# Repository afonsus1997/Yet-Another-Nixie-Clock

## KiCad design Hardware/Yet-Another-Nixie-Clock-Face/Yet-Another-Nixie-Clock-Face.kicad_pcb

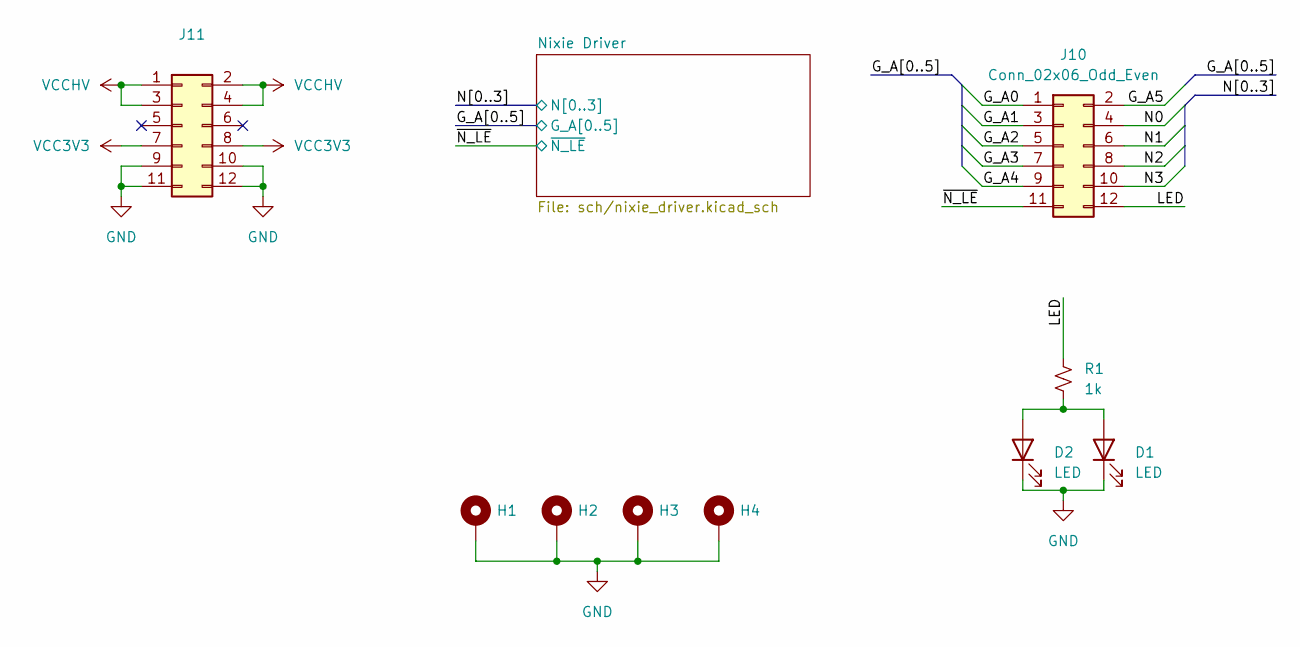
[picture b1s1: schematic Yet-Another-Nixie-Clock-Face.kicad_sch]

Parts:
D1, D2: LED; LED_0603_1608Metric
H1, H2, H3, H4: MountingHole_Pad; MountingHole_3.2mm_M3_Pad
J10, J11: Conn_02x06_Odd_Even; PinHeader_2x06_P2.54mm_Vertical_SMD; LCSC C3294464
R1: 1k; R_0603_1608Metric; LCSC C22548

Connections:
/G_A0: J10.1; also elsewhere on the board
/G_A1: J10.3; also elsewhere on the board
/G_A2: J10.5; also elsewhere on the board
/G_A3: J10.7; also elsewhere on the board
/G_A4: J10.9; also elsewhere on the board
/G_A5: J10.2; also elsewhere on the board
/LED: J10.12, R1.2
/N0: J10.4; also elsewhere on the board
/N1: J10.6; also elsewhere on the board
/N2: J10.8; also elsewhere on the board
/N3: J10.10; also elsewhere on the board
/~N_LE: J10.11; also elsewhere on the board
GND: D1.1 (K), D2.1 (K), H1.1, H2.1, H3.1, H4.1, J11.9, J11.10, J11.11, J11.12; also elsewhere on the board
unnamed: D1.2 (A), D2.2 (A), R1.1
VCC3V3: J11.7, J11.8; also elsewhere on the board
VCCHV: J11.1, J11.2, J11.3, J11.4; also elsewhere on the board

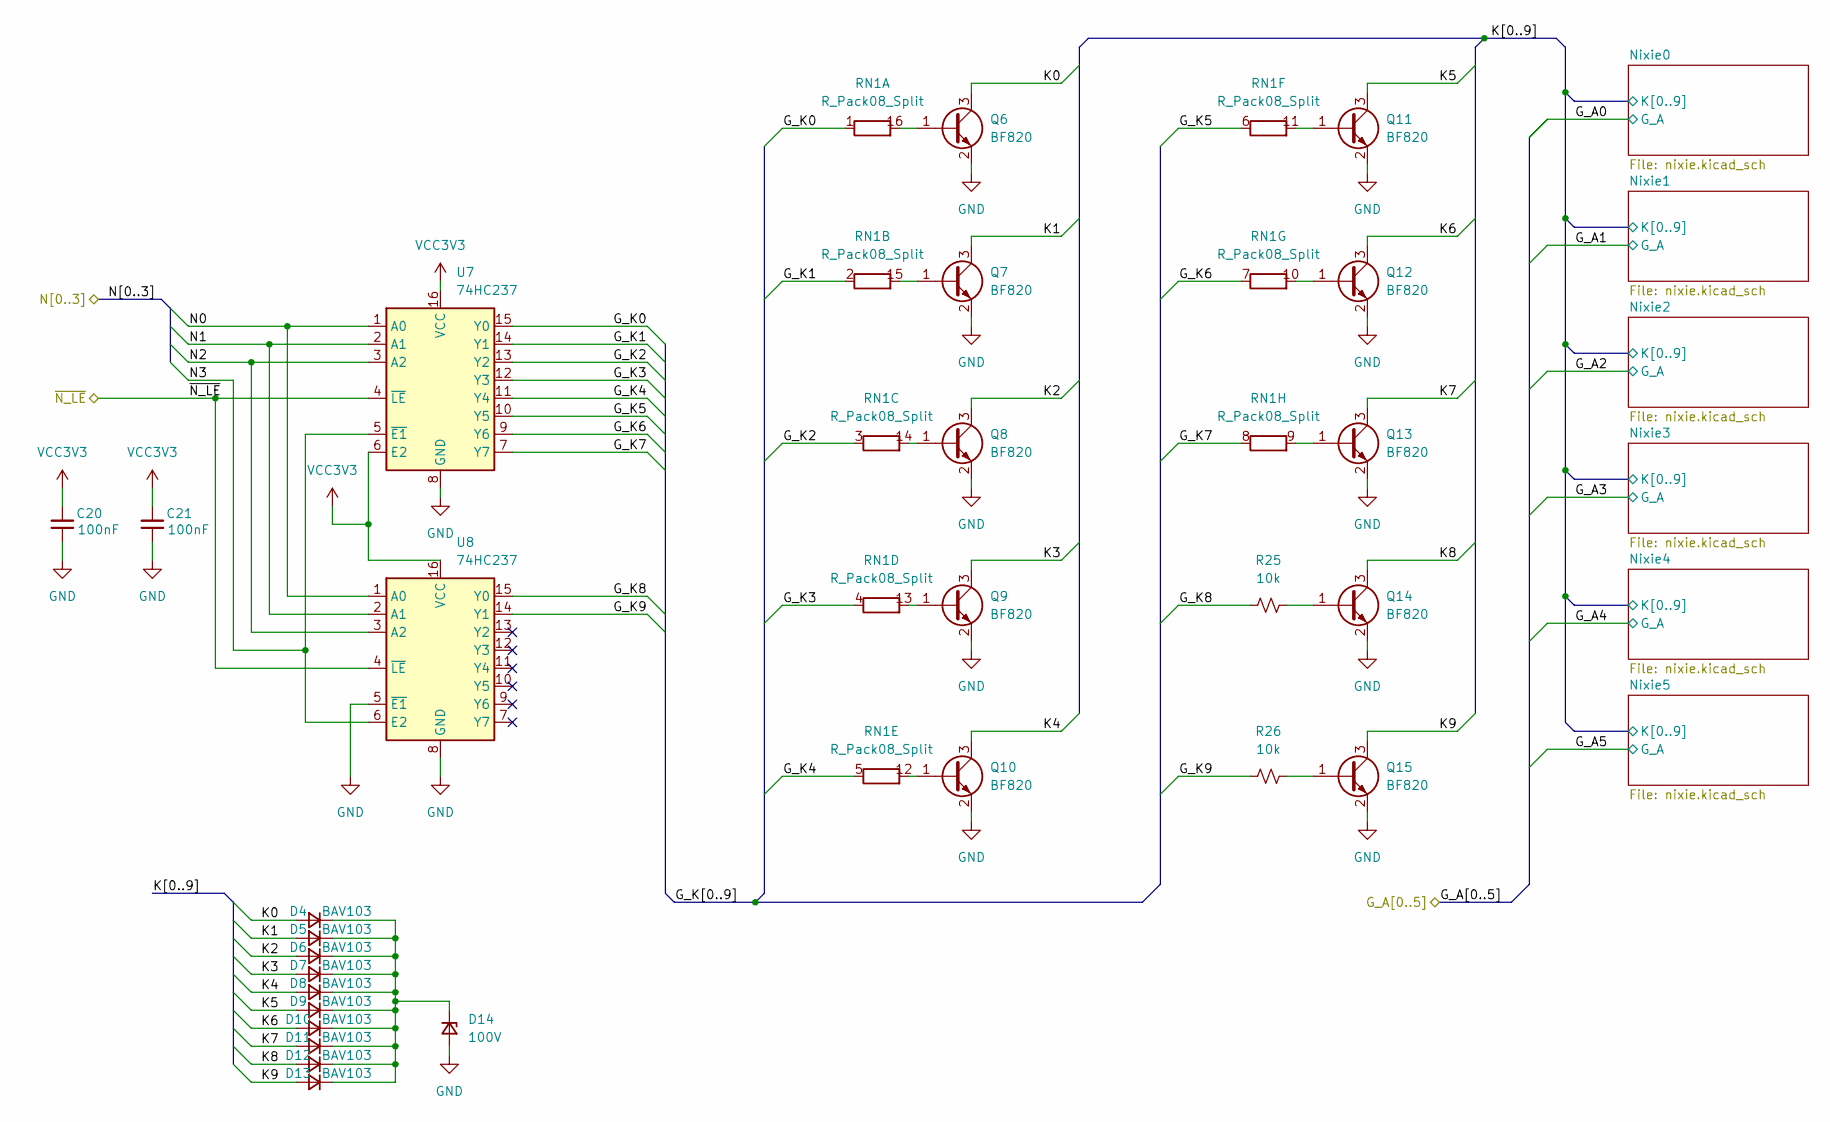
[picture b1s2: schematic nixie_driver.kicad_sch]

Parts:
C20, C21: 100nF; C_0603_1608Metric; LCSC C92490
D4, D5, D6, D7, D8, D9, D10, D11, D12, D13: BAV103; D_MiniMELF; LCSC C3313132
D14: 100V; D_SMA; LCSC C3014322
Q6, Q7, Q8, Q9, Q10, Q11, Q12, Q13, Q14, Q15: BF820; TSOT-23; LCSC C426796
R25, R26: 10k; R_0603_1608Metric; LCSC C98220
RN1: R_Pack08_Split; RES-ARRAY-SMD_0402-16P-L4.0-W1.6-BL-2; LCSC C326649
U7, U8: 74HC237; TSSOP-16_4.4x5mm_P0.65mm; LCSC C2674656

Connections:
/N0: U7.1 (A0), U8.1 (A0); also elsewhere on the board
/N1: U7.2 (A1), U8.2 (A1); also elsewhere on the board
/N2: U7.3 (A2), U8.3 (A2); also elsewhere on the board
/N3: U7.5 (~E1), U8.6 (E2); also elsewhere on the board
/Nixie Driver/G_K0: RN1.1 (R1.1), U7.15 (Y0)
/Nixie Driver/G_K1: RN1.2 (R2.1), U7.14 (Y1)
/Nixie Driver/G_K2: RN1.3 (R3.1), U7.13 (Y2)
/Nixie Driver/G_K3: RN1.4 (R4.1), U7.12 (Y3)
/Nixie Driver/G_K4: RN1.5 (R5.1), U7.11 (Y4)
/Nixie Driver/G_K5: RN1.6 (R6.1), U7.10 (Y5)
/Nixie Driver/G_K6: RN1.7 (R7.1), U7.9 (Y6)
/Nixie Driver/G_K7: RN1.8 (R8.1), U7.7 (Y7)
/Nixie Driver/G_K8: R25.1, U8.15 (Y0)
/Nixie Driver/G_K9: R26.1, U8.14 (Y1)
/Nixie Driver/K0: D4.2 (A), Q6.3 (C); also elsewhere on the board
/Nixie Driver/K1: D5.2 (A), Q7.3 (C); also elsewhere on the board
/Nixie Driver/K2: D6.2 (A), Q8.3 (C); also elsewhere on the board
/Nixie Driver/K3: D7.2 (A), Q9.3 (C); also elsewhere on the board
/Nixie Driver/K4: D8.2 (A), Q10.3 (C); also elsewhere on the board
/Nixie Driver/K5: D9.2 (A), Q11.3 (C); also elsewhere on the board
/Nixie Driver/K6: D10.2 (A), Q12.3 (C); also elsewhere on the board
/Nixie Driver/K7: D11.2 (A), Q13.3 (C); also elsewhere on the board
/Nixie Driver/K8: D12.2 (A), Q14.3 (C); also elsewhere on the board
/Nixie Driver/K9: D13.2 (A), Q15.3 (C); also elsewhere on the board
/~N_LE: U7.4 (~LE), U8.4 (~LE); also elsewhere on the board
GND: C20.1, C21.1, D14.2 (A), Q6.2 (E), Q7.2 (E), Q8.2 (E), Q9.2 (E), Q10.2 (E), Q11.2 (E), Q12.2 (E), Q13.2 (E), Q14.2 (E), Q15.2 (E), U7.8 (GND), U8.5 (~E1), U8.8 (GND); also elsewhere on the board
unnamed: D4.1 (K), D5.1 (K), D6.1 (K), D7.1 (K), D8.1 (K), D9.1 (K), D10.1 (K), D11.1 (K), D12.1 (K), D13.1 (K), D14.1 (K)
unnamed: Q6.1 (B), RN1.16 (R1.2)
unnamed: Q7.1 (B), RN1.15 (R2.2)
unnamed: Q8.1 (B), RN1.14 (R3.2)
unnamed: Q9.1 (B), RN1.13 (R4.2)
unnamed: Q10.1 (B), RN1.12 (R5.2)
unnamed: Q11.1 (B), RN1.11 (R6.2)
unnamed: Q12.1 (B), RN1.10 (R7.2)
unnamed: Q13.1 (B), RN1.9 (R8.2)
unnamed: Q14.1 (B), R25.2
unnamed: Q15.1 (B), R26.2
VCC3V3: C20.2, C21.2, U7.6 (E2), U7.16 (VCC), U8.16 (VCC); also elsewhere on the board

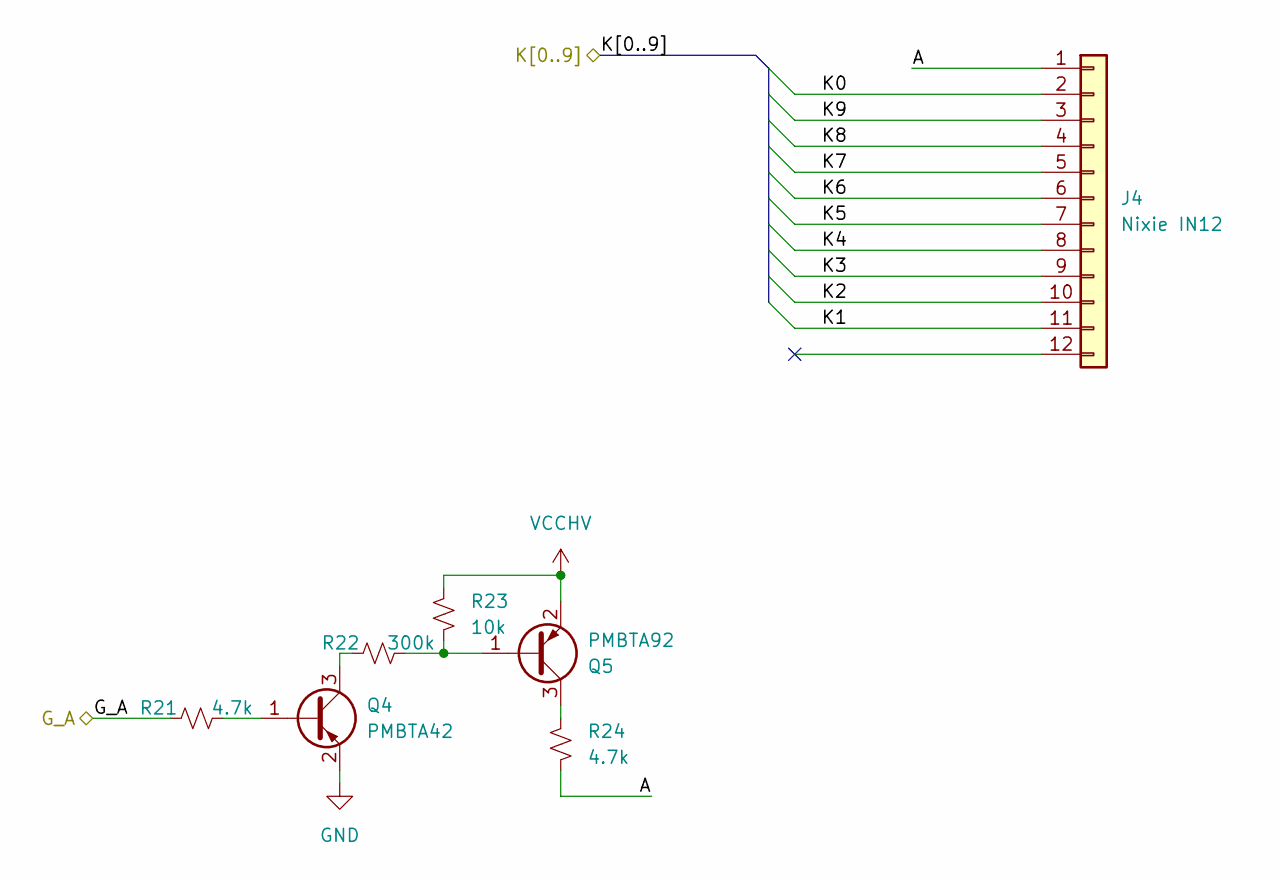
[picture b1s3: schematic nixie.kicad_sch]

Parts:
J4: Nixie IN12; IN_12B_Socket
Q4: PMBTA42; SOT-23; LCSC C417384
Q5: PMBTA92; SOT-23; LCSC C282560
R21, R24: 4.7k; R_0603_1608Metric; LCSC C99782
R22: 300k; R_0603_1608Metric; LCSC C114667
R23: 10k; R_0603_1608Metric; LCSC C98220

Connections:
/G_A0: R21.2; also elsewhere on the board
/Nixie Driver/K0: J4.2; also elsewhere on the board
/Nixie Driver/K1: J4.11; also elsewhere on the board
/Nixie Driver/K2: J4.10; also elsewhere on the board
/Nixie Driver/K3: J4.9; also elsewhere on the board
/Nixie Driver/K4: J4.8; also elsewhere on the board
/Nixie Driver/K5: J4.7; also elsewhere on the board
/Nixie Driver/K6: J4.6; also elsewhere on the board
/Nixie Driver/K7: J4.5; also elsewhere on the board
/Nixie Driver/K8: J4.4; also elsewhere on the board
/Nixie Driver/K9: J4.3; also elsewhere on the board
/Nixie Driver/Nixie0/A: J4.1, R24.2
GND: Q4.2 (E); also elsewhere on the board
unnamed: Q4.1 (B), R21.1
unnamed: Q4.3 (C), R22.2
unnamed: Q5.1 (B), R22.1, R23.2
unnamed: Q5.3 (C), R24.1
VCCHV: Q5.2 (E), R23.1; also elsewhere on the board

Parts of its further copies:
J5, J6, J7, J8, J9: Nixie IN12; IN_12B_Socket
Q16, Q18, Q20, Q22, Q24: PMBTA42; SOT-23; LCSC C417384
Q17, Q19, Q21, Q23, Q25: PMBTA92; SOT-23; LCSC C282560
R27, R30, R31, R34, R35, R38, R39, R42, R43, R46: 4.7k; R_0603_1608Metric; LCSC C99782
R28, R32, R36, R40, R44: 300k; R_0603_1608Metric; LCSC C114667
R29, R33, R37, R41, R45: 10k; R_0603_1608Metric; LCSC C98220

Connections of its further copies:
/G_A1: R27.2; also elsewhere on the board
/G_A2: R31.2; also elsewhere on the board
/G_A3: R35.2; also elsewhere on the board
/G_A4: R39.2; also elsewhere on the board
/G_A5: R43.2; also elsewhere on the board
/Nixie Driver/K0: J5.2, J6.2, J7.2, J8.2, J9.2; also elsewhere on the board
/Nixie Driver/K1: J5.11, J6.11, J7.11, J8.11, J9.11; also elsewhere on the board
/Nixie Driver/K2: J5.10, J6.10, J7.10, J8.10, J9.10; also elsewhere on the board
/Nixie Driver/K3: J5.9, J6.9, J7.9, J8.9, J9.9; also elsewhere on the board
/Nixie Driver/K4: J5.8, J6.8, J7.8, J8.8, J9.8; also elsewhere on the board
/Nixie Driver/K5: J5.7, J6.7, J7.7, J8.7, J9.7; also elsewhere on the board
/Nixie Driver/K6: J5.6, J6.6, J7.6, J8.6, J9.6; also elsewhere on the board
/Nixie Driver/K7: J5.5, J6.5, J7.5, J8.5, J9.5; also elsewhere on the board
/Nixie Driver/K8: J5.4, J6.4, J7.4, J8.4, J9.4; also elsewhere on the board
/Nixie Driver/K9: J5.3, J6.3, J7.3, J8.3, J9.3; also elsewhere on the board
/Nixie Driver/Nixie1/A: J5.1, R30.2
/Nixie Driver/Nixie2/A: J6.1, R34.2
/Nixie Driver/Nixie3/A: J7.1, R38.2
/Nixie Driver/Nixie4/A: J8.1, R42.2
/Nixie Driver/Nixie5/A: J9.1, R46.2
GND: Q16.2 (E), Q18.2 (E), Q20.2 (E), Q22.2 (E), Q24.2 (E); also elsewhere on the board
unnamed: Q16.1 (B), R27.1
unnamed: Q16.3 (C), R28.2
unnamed: Q17.1 (B), R28.1, R29.2
unnamed: Q17.3 (C), R30.1
unnamed: Q18.1 (B), R31.1
unnamed: Q18.3 (C), R32.2
unnamed: Q19.1 (B), R32.1, R33.2
unnamed: Q19.3 (C), R34.1
unnamed: Q20.1 (B), R35.1
unnamed: Q20.3 (C), R36.2
unnamed: Q21.1 (B), R36.1, R37.2
unnamed: Q21.3 (C), R38.1
unnamed: Q22.1 (B), R39.1
unnamed: Q22.3 (C), R40.2
unnamed: Q23.1 (B), R40.1, R41.2
unnamed: Q23.3 (C), R42.1
unnamed: Q24.1 (B), R43.1
unnamed: Q24.3 (C), R44.2
unnamed: Q25.1 (B), R44.1, R45.2
unnamed: Q25.3 (C), R46.1
VCCHV: Q17.2 (E), Q19.2 (E), Q21.2 (E), Q23.2 (E), Q25.2 (E), R29.1, R33.1, R37.1, R41.1, R45.1; also elsewhere on the board

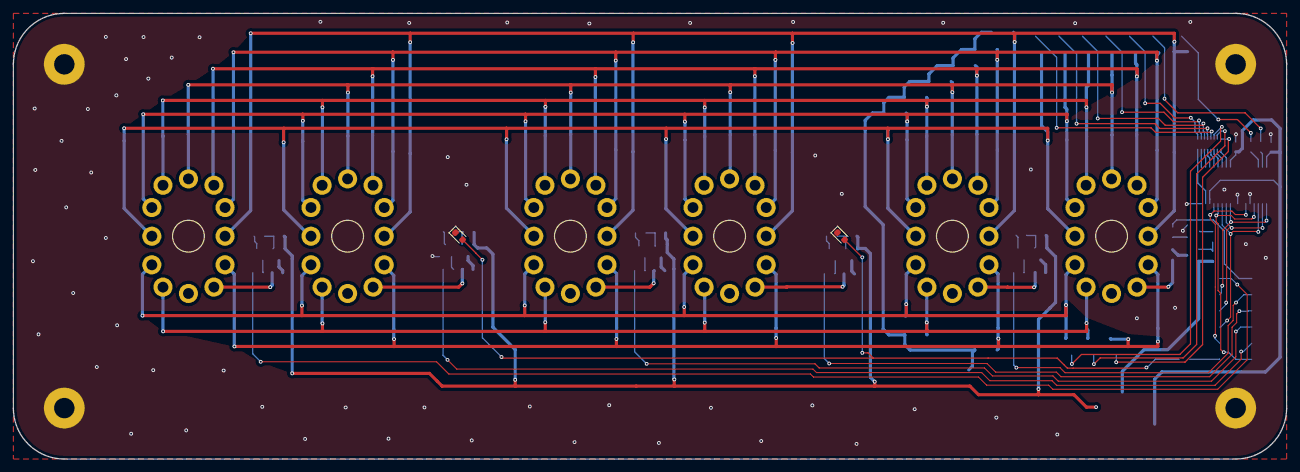
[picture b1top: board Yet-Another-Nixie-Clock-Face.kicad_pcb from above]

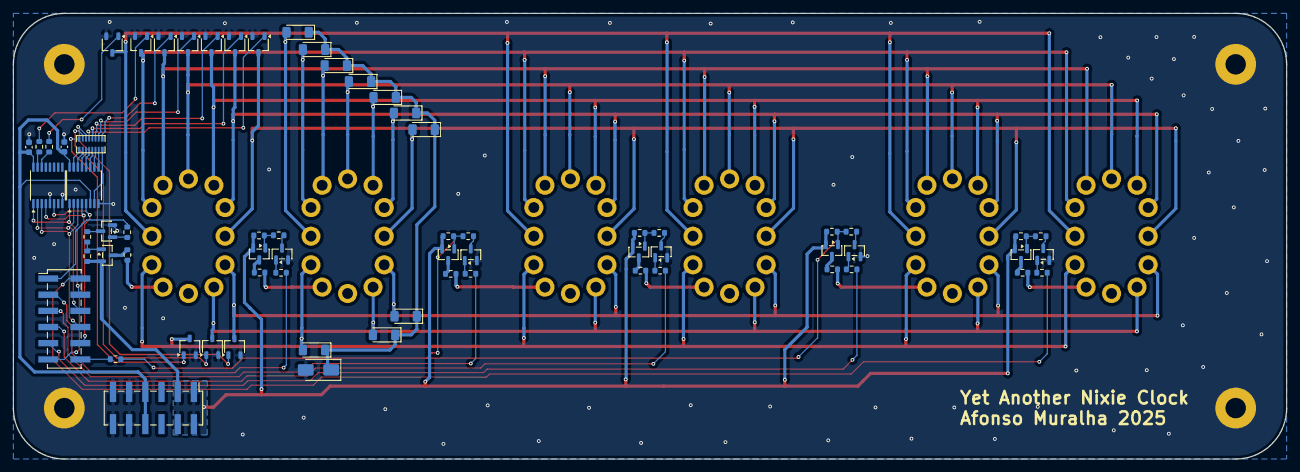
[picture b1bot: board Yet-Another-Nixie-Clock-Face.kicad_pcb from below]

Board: 2 copper layers, 200.0 x 70.0 mm, 79 parts (67 on the bottom side), 77 nets.

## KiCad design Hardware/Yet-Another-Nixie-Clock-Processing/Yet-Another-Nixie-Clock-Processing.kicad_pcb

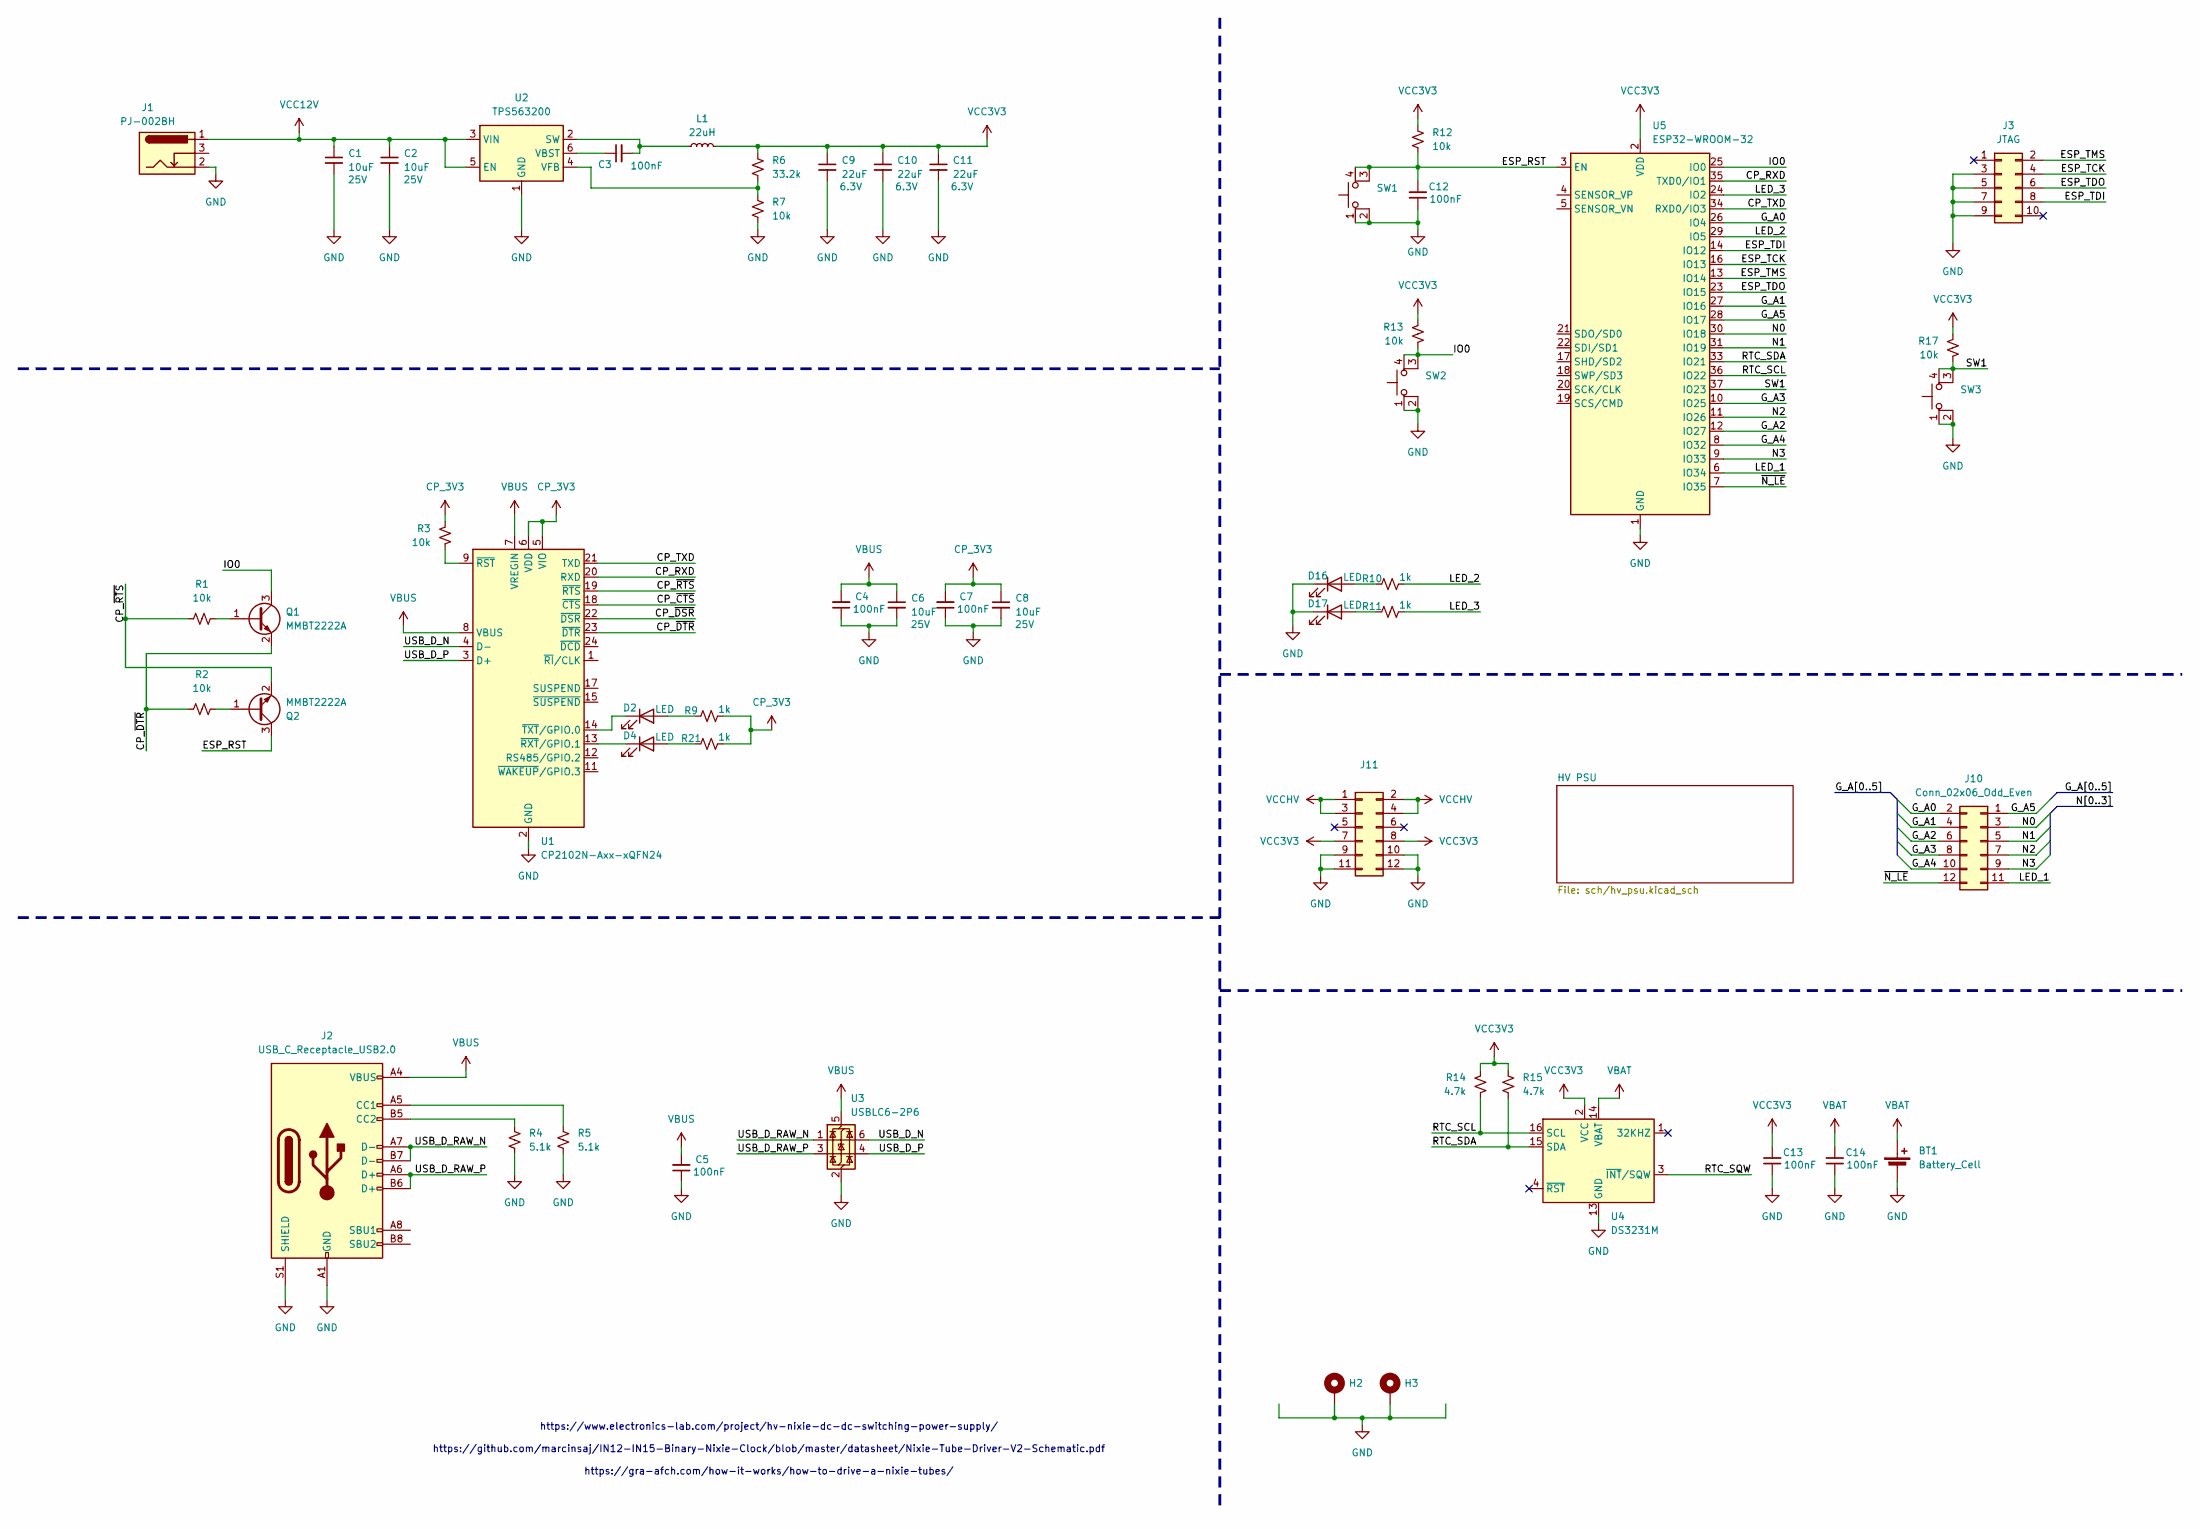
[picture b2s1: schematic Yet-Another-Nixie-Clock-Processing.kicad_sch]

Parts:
BT1: Battery_Cell; BAT-TH_CR2032-BS-6-1
C1, C2, C6, C8: 10uF; C_0603_1608Metric; Voltage 25V; LCSC C96446
C3, C4, C5, C7, C12, C13, C14: 100nF; C_0603_1608Metric; LCSC C92490
C9, C10, C11: 22uF; C_0603_1608Metric; Voltage 6.3V; LCSC C109448
D2, D4, D16, D17: LED; LED_0603_1608Metric
H2, H3: MountingHole_Pad; MountingHole_3.2mm_M3_Pad
J1: PJ-002BH; CUI_PJ-002BH; MANUFACTURER_PART_NUMBER PJ-002BH; LCSC C22359705
J2: USB_C_Receptacle_USB2.0; USB_C_Receptacle_HCTL_HC-TYPE-C-16P-01A; LCSC C2894897
J3: JTAG; IDC-Header_2x05_P2.54mm_Vertical; LCSC C573025
J10, J11: Conn_02x06_Odd_Even; PinHeader_2x06_P2.54mm_Vertical_SMD; LCSC C2685123
L1: 22uH; L_APV_APH0615; LCSC C842909
Q1, Q2: MMBT2222A; SOT-23; LCSC C82460
R1, R2, R3, R7, R12, R13, R17: 10k; R_0603_1608Metric; LCSC C98220
R4, R5: 5.1k; R_0402_1005Metric; LCSC C407575
R6: 33.2k; R_0603_1608Metric; LCSC C706161
R9, R10, R11, R21: 1k; R_0603_1608Metric; LCSC C22548
R14, R15: 4.7k; R_0603_1608Metric; LCSC C99782
SW1, SW2, SW3: SW_MEC_5E; SW_SKRPACE010; LCSC C139797
U1: CP2102N-Axx-xQFN24; QFN-24-1EP_4x4mm_P0.5mm_EP2.6x2.6mm; LCSC C969151
U2: TPS563200; SOT-23-6; LCSC C97253
U3: USBLC6-2P6; SOT-666; LCSC C2827693
U4: DS3231M; SOIC-16W_7.5x10.3mm_P1.27mm; LCSC C722467
U5: ESP32-WROOM-32; LCSC C82899

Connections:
/CP_RXD: U1.20 (RXD), U5.35 (TXD0/IO1)
/CP_TXD: U1.21 (TXD), U5.34 (RXD0/IO3)
/CP_~CTS: U1.18 (~CTS)
/CP_~DSR: U1.22 (~DSR)
/CP_~DTR: Q1.2 (E), R2.1, U1.23 (~DTR)
/CP_~RTS: Q2.2 (E), R1.1, U1.19 (~RTS)
/ESP_RST: C12.2, Q2.3 (C), R12.2, SW1.3 (K), SW1.4 (A), U5.3 (EN)
/ESP_TCK: J3.4, U5.16 (IO13)
/ESP_TDI: J3.8, U5.14 (IO12)
/ESP_TDO: J3.6, U5.23 (IO15)
/ESP_TMS: J3.2, U5.13 (IO14)
/G_A0: J10.2, U5.26 (IO4)
/G_A1: J10.4, U5.27 (IO16)
/G_A2: J10.6, U5.12 (IO27)
/G_A3: J10.8, U5.10 (IO25)
/G_A4: J10.10, U5.8 (IO32)
/G_A5: J10.1, U5.28 (IO17)
/IO0: Q1.3 (C), R13.2, SW2.3 (K), SW2.4 (A), U5.25 (IO0)
/LED_1: J10.11, U5.6 (IO34)
/LED_2: R10.1, U5.29 (IO5)
/LED_3: R11.1, U5.24 (IO2)
/N0: J10.3, U5.30 (IO18)
/N1: J10.5, U5.31 (IO19)
/N2: J10.7, U5.11 (IO26)
/N3: J10.9, U5.9 (IO33)
/RTC_SCL: R14.2, U4.16 (SCL), U5.36 (IO22)
/RTC_SDA: R15.2, U4.15 (SDA), U5.33 (IO21)
/RTC_SQW: U4.3 (~INT/SQW)
/SW1: R17.2, SW3.3 (K), SW3.4 (A), U5.37 (IO23)
/USB_D_N: U1.4 (D-), U3.6 (I/O1)
/USB_D_P: U1.3 (D+), U3.4 (I/O2)
/USB_D_RAW_N: J2.A7 (D-), J2.B7 (D-), U3.1 (I/O1)
/USB_D_RAW_P: J2.A6 (D+), J2.B6 (D+), U3.3 (I/O2)
/~N_LE: J10.12, U5.7 (IO35)
CP_3V3: C7.2, C8.1, R3.1, R9.1, R21.1, U1.5 (VIO), U1.6 (VDD)
GND: BT1.2 (-), C1.2, C2.2, C4.1, C5.1, C6.2, C7.1, C8.2, C9.2, C10.2, C11.2, C12.1, C13.1, C14.1, D16.1 (K), D17.1 (K), H2.1, H3.1, J1.2, J2.A1 (GND), J2.A12 (GND), J2.B1 (GND), J2.B12 (GND), J2.S1 (SHIELD), J3.3, J3.5, J3.7, J3.9, J11.9, J11.10, J11.11, J11.12, R4.2, R5.2, R7.2, SW1.1, SW1.2, SW2.1, SW2.2, SW3.1, SW3.2, U1.2 (GND), U1.25 (GND), U2.1 (GND), U3.2 (GND), U4.5 (GND), U4.6 (GND), U4.7 (GND), U4.8 (GND), U4.9 (GND), U4.10 (GND), U4.11 (GND), U4.12 (GND), U4.13 (GND), U5.1 (GND), U5.15 (GND), U5.38 (GND), U5.39 (GND); also elsewhere on the board
unnamed: D2.2 (A), R9.2
unnamed: D2.1 (K), U1.14 (~TXT/GPIO.0)
unnamed: D4.2 (A), R21.2
unnamed: D4.1 (K), U1.13 (~RXT/GPIO.1)
unnamed: D16.2 (A), R10.2
unnamed: D17.2 (A), R11.2
unnamed: J2.A5 (CC1), R5.1
unnamed: J2.B5 (CC2), R4.1
unnamed: Q1.1 (B), R1.2
unnamed: Q2.1 (B), R2.2
unnamed: R3.2, U1.9 (~RST)
unnamed: C3.2, L1.1, U2.2 (SW)
unnamed: C3.1, U2.6 (VBST)
unnamed: R6.2, R7.1, U2.4 (VFB)
VBAT: BT1.1 (+), C14.2, U4.14 (VBAT)
VBUS: C4.2, C5.2, C6.1, J2.A4 (VBUS), J2.A9 (VBUS), J2.B4 (VBUS), J2.B9 (VBUS), U1.7 (VREGIN), U1.8 (VBUS), U3.5 (VBUS)
VCC3V3: C9.1, C10.1, C11.1, C13.2, J11.7, J11.8, L1.2, R6.1, R12.1, R13.1, R14.1, R15.1, R17.1, U4.2 (VCC), U5.2 (VDD)
VCC12V: C1.1, C2.1, J1.1, U2.3 (VIN), U2.5 (EN); also elsewhere on the board
VCCHV: J11.1, J11.2, J11.3, J11.4; also elsewhere on the board

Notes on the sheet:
https://www.electronics-lab.com/project/hv-nixie-dc-dc-switching-power-supply/ https://github.com/marcinsaj/IN12-IN15-Binary-Nixie-Clock/blob/master/datasheet/Nixie-Tube-Driver-V2-Schematic.pdf https://gra-afch.com/how-it-works/how-to-drive-a-nixie-tubes/

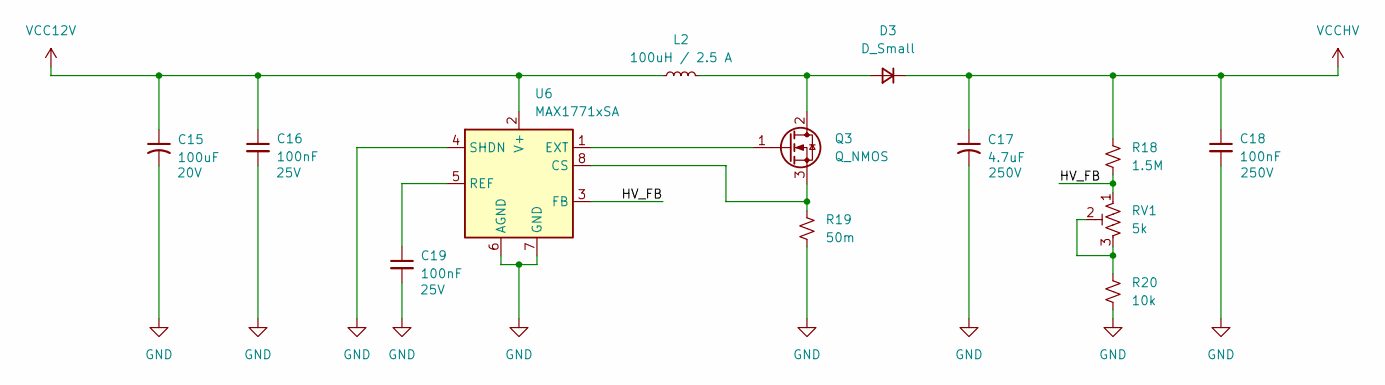
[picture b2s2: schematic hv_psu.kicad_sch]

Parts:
C15: 100uF; CP_EIA-7343-15_Kemet-W_HandSolder; Voltage 20V; LCSC C122302
C16, C19: 100nF; C_0603_1608Metric; Voltage 25V; LCSC C92490
C17: 4.7uF; C_Elec_8x10.2; Voltage 250V; LCSC C88702
C18: 100nF; C_1210_3225Metric; Voltage 250V; LCSC C52020
D3: D_Small; D_SMB_Handsoldering; LCSC C145321
L2: 100uH / 2.5 A; L_APV_APH0840; LCSC C2962892
Q3: Q_NMOS; TO-263-2; LCSC C39238
R18: 1.5M; R_0805_2012Metric; LCSC C118025
R19: 50m; R_1206_3216Metric; LCSC C149662
R20: 10k; R_0805_2012Metric; LCSC C269724
RV1: 5k; Potentiometer_Bourns_3314G_Vertical; LCSC C719180
U6: MAX1771xSA; SO-8_3.9x4.9mm_P1.27mm; LCSC C407903

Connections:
/HV PSU/HV_FB: R18.2, RV1.1, U6.3 (FB)
GND: C15.2, C16.2, C17.2, C18.2, C19.2, R19.2, R20.2, U6.4 (SHDN), U6.6 (AGND), U6.7 (GND); also elsewhere on the board
unnamed: D3.2 (A), L2.2, Q3.2 (D)
unnamed: Q3.1 (G), U6.1 (EXT)
unnamed: Q3.3 (S), R19.1, U6.8 (CS)
unnamed: R20.1, RV1.2, RV1.3
unnamed: C19.1, U6.5 (REF)
VCC12V: C15.1, C16.1, L2.1, U6.2 (V+); also elsewhere on the board
VCCHV: C17.1, C18.1, D3.1 (K), R18.1; also elsewhere on the board

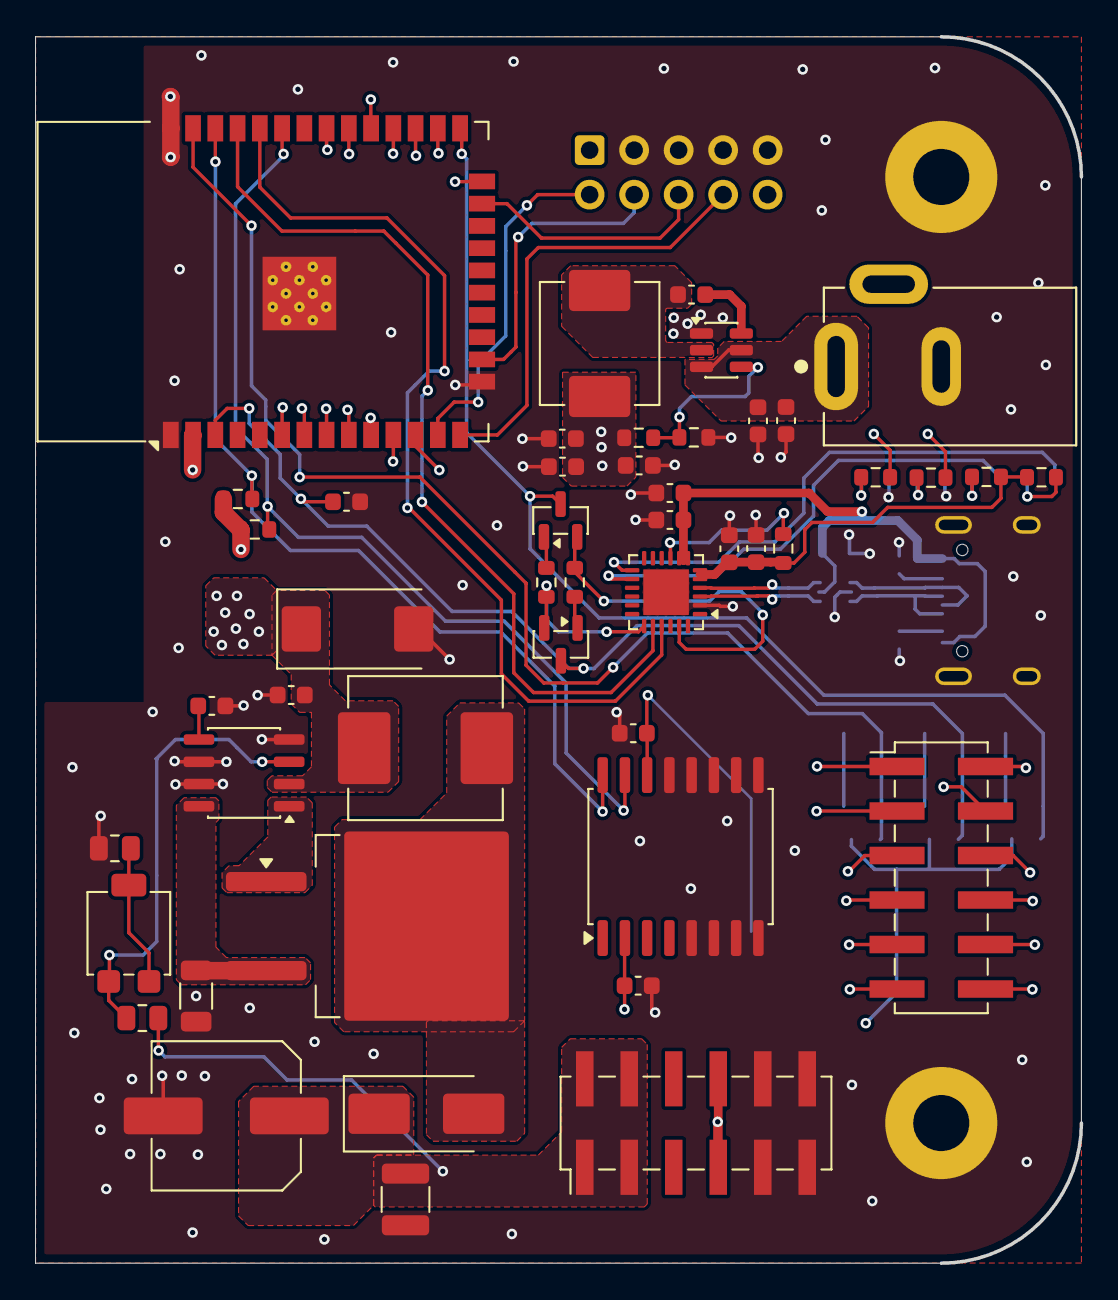
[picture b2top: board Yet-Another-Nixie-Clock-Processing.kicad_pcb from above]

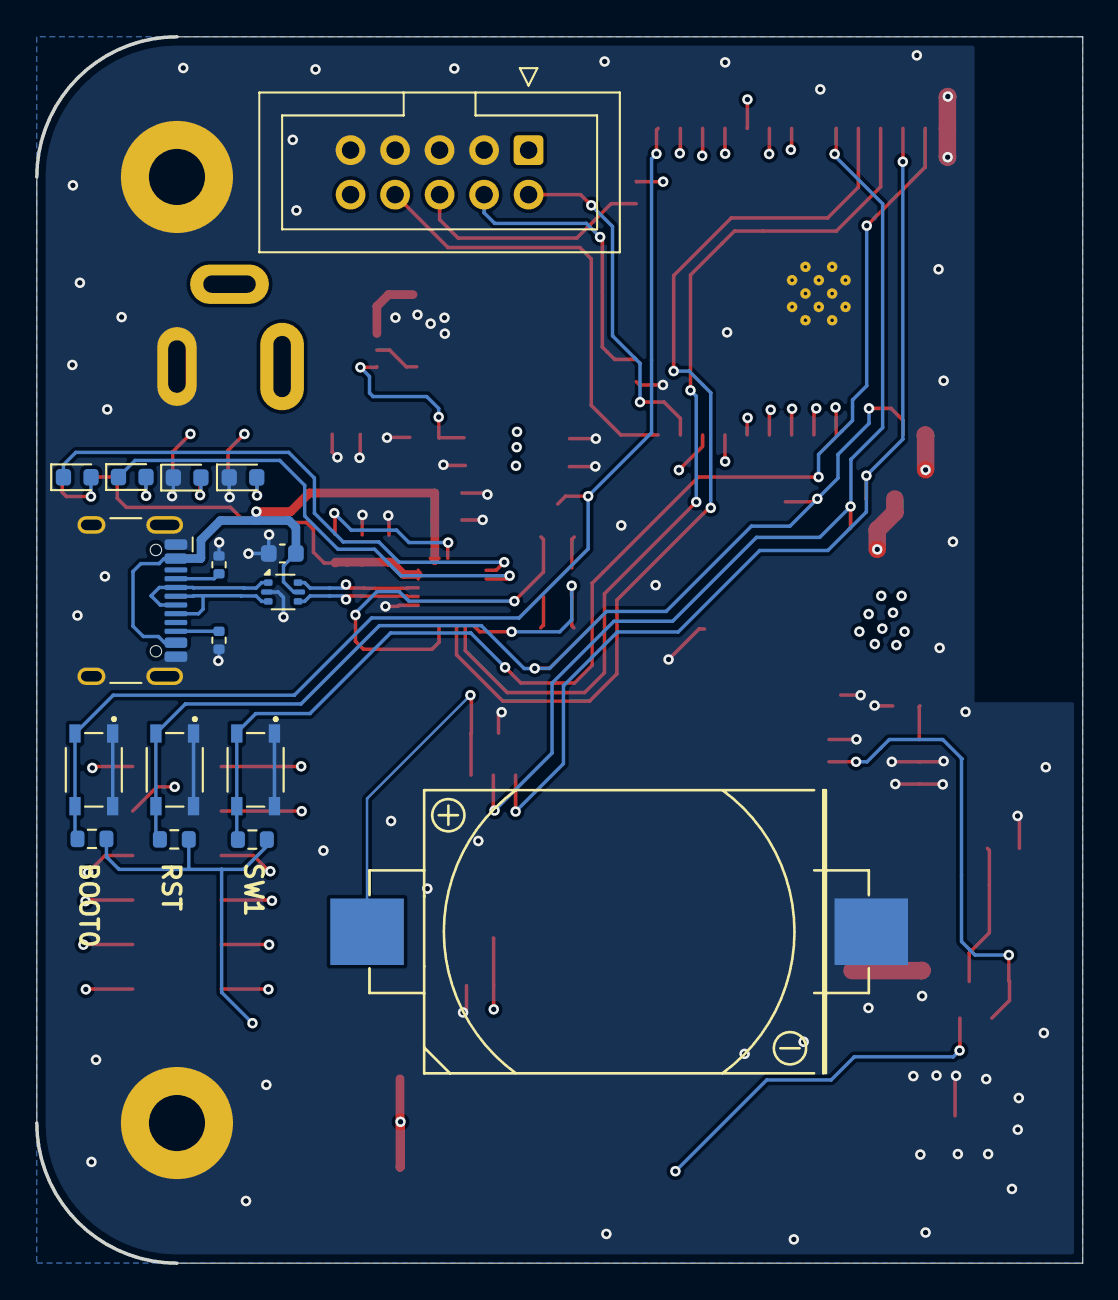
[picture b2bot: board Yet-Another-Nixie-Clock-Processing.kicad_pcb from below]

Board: 4 copper layers, 59.6 x 70.0 mm, 66 parts (17 on the bottom side), 58 nets.

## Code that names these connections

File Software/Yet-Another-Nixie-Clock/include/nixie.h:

#ifndef __NIXIE__H__
#define __NIXIE__H__

#include <Arduino.h>

#define G_A0 4
#define G_A1 16
#define G_A2 27
#define G_A3 25
#define G_A4 32
#define G_A5 17

#define N0 18
#define N1 19
#define N2 26
#define N3 33

#define N_LE 35

void setupNixie();
void enableDigit(uint8_t digit);
void setDecoderOutput(uint8_t value);
void updateTime();
void setTime(uint8_t hours, uint8_t minutes, uint8_t seconds);
void disableDigits();
void disableDigit(uint8_t digit);
void nixieLoop();
void multiplexNixie();

#endif  //!__NIXIE__H__

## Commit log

2025-10-25 Schematic advancements
2025-10-25 Schematic work
2025-10-25 Schematic work and fixes
2025-10-27 Schematic advancements, separated boards
2025-10-27 Removed old board
2025-10-27 Minor improvements
2025-10-28 Major schematic and layout advancements
2025-10-29 Minor touches. Fixed bom. Exported production files
2025-11-28 Added software boilerplate
2025-11-28 Software work
2025-12-03 Writing to nixies work
2025-12-03 Moved nixie processing to other core
2025-12-03 Started adding provisioning
2025-12-05 improvements
2025-12-05 removed submodules
2025-12-05 add submodule
2025-12-05 checkout submodule
2025-12-05 Provisioning works
2025-12-07 minor change
2025-12-07 Started adding lwbtn
2025-12-07 Lwbtn work
2025-12-07 Started adding RTC
2025-12-07 RTC work
2025-12-16 RTC and clock working
